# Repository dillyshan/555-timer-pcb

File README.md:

# 555-timer-pcb
A 555 timer PCB designed in KiCad.

## Project Overview

This is my first PCB design project, created to learn the complete PCB design workflow using KiCad. The circuit uses an NE555 timer in astable mode to generate a repeating output signal that drives an LED.

The project covers schematic design, footprint assignment, PCB layout, component placement, routing, ground planes, ERC/DRC verification, and manufacturing file generation.

## Features

- NE555 timer configured in astable mode
- LED output indicator
- Through-hole components for easy assembly
- 5 V power input
- Ground plane for GND connections
- PCB designed and routed in KiCad
- ERC and DRC verified

## Components

- NE555 timer IC
- 10 kΩ resistor
- 100 kΩ resistor
- 1 kΩ LED current-limiting resistor
- 10 µF electrolytic capacitor
- 10 nF capacitor
- 100 nF decoupling capacitor
- LED
- 2-pin power connector

## How It Works

The NE555 timer is configured in astable mode, meaning it continuously switches between HIGH and LOW without requiring an external trigger. R1, R2, and C1 control the timing of the oscillation.

As C1 repeatedly charges and discharges, the NE555 output at pin 3 switches between HIGH and LOW. The output drives the LED through R3, causing the LED to blink.

C2 and C3 are used for stability and noise filtering.

## Design Process

1. Created the NE555 astable timer schematic in KiCad.
2. Ran ERC to check the schematic for electrical errors.
3. Assigned through-hole footprints to each component.
4. Created the PCB board outline and placed the components.
5. Routed the signal and power traces.
6. Added a copper ground plane connected to GND.
7. Ran DRC and schematic parity checks to verify the final PCB layout.

## PCB 3D View

## What I Learned

Through this project, I learned how to:

- Create and verify a schematic in KiCad
- Select and assign component footprints
- Place components with routing and assembly in mind
- Route signal and power traces
- Use net classes to define different trace widths
- Create a copper ground plane
- Use ERC and DRC to identify design issues
- Inspect a completed PCB using KiCad's 3D Viewer
- Prepare a PCB design for manufacturing

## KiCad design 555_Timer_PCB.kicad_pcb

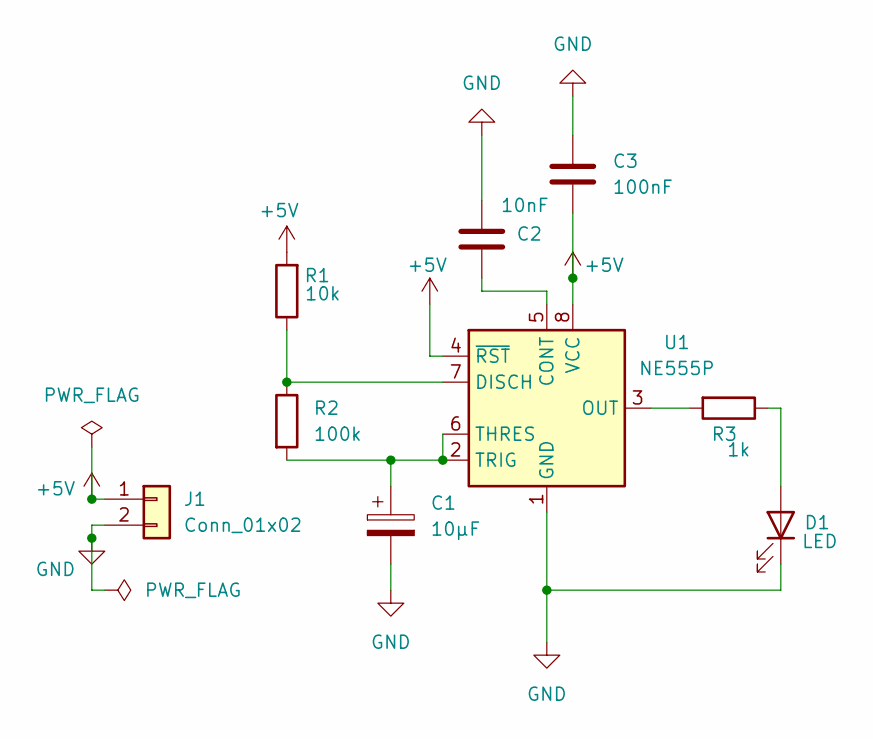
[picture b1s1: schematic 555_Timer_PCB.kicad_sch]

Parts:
C1: 10μF; CP_Radial_D5.0mm_P2.00mm
C2: 10nF; C_Disc_D5.0mm_W2.5mm_P5.00mm
C3: 100nF; C_Disc_D5.0mm_W2.5mm_P5.00mm
D1: LED; LED_D5.0mm
J1: Conn_01x02; PinHeader_1x02_P2.54mm_Vertical
R1: 10k; R_Axial_DIN0207_L6.3mm_D2.5mm_P10.16mm_Horizontal
R2: 100k; R_Axial_DIN0207_L6.3mm_D2.5mm_P10.16mm_Horizontal
R3: 1k; R_Axial_DIN0207_L6.3mm_D2.5mm_P10.16mm_Horizontal
U1: NE555P; DIP-8_W7.62mm

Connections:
+5V: C3.2, J1.1, R1.2, U1.4 (~RST), U1.8 (VCC)
GND: C1.2, C2.1, C3.1, D1.1 (K), J1.2, U1.1 (GND)
unnamed: D1.2 (A), R3.1
unnamed: C2.2, U1.5 (CONT)
unnamed: R1.1, R2.1, U1.7 (DISCH)
unnamed: R3.2, U1.3 (OUT)
unnamed: C1.1, R2.2, U1.2 (TRIG), U1.6 (THRES)

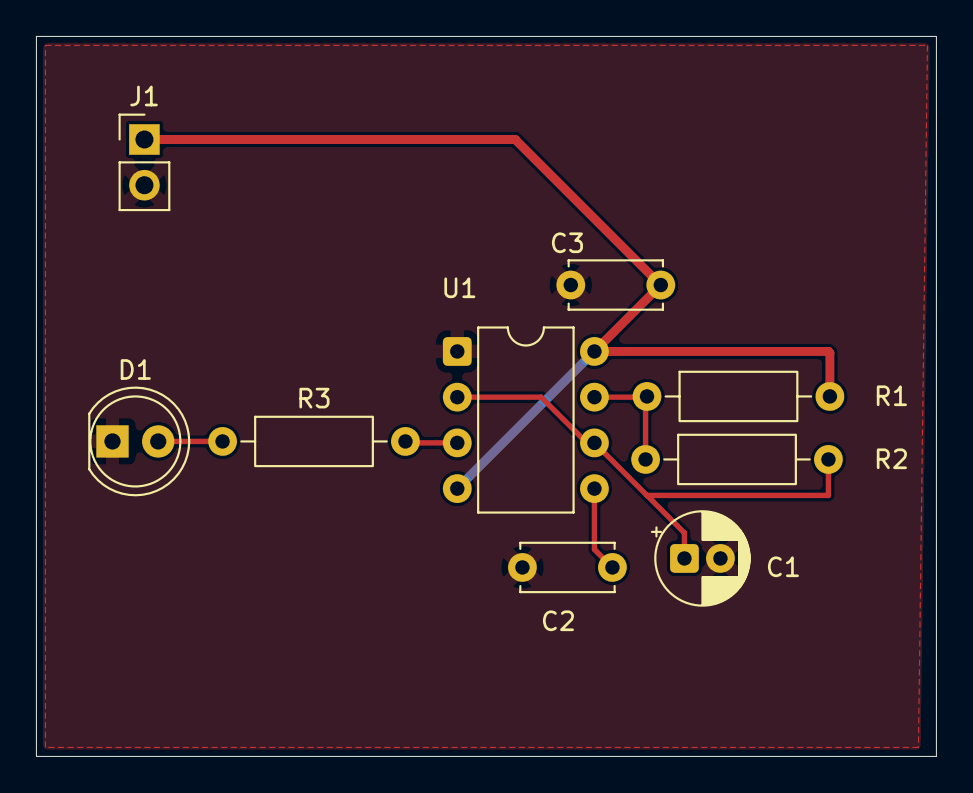
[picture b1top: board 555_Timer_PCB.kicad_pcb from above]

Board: 2 copper layers, 50.0 x 40.0 mm, 9 parts (0 on the bottom side), 7 nets.
